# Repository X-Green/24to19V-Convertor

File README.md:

# 24to19V-Convertor

synchronous buck converter

## Chip Used

**LM3150** *From Texas Instruments* : Controller IC

**BSC070N10NS5** *From Infineon* : NMOS for switching

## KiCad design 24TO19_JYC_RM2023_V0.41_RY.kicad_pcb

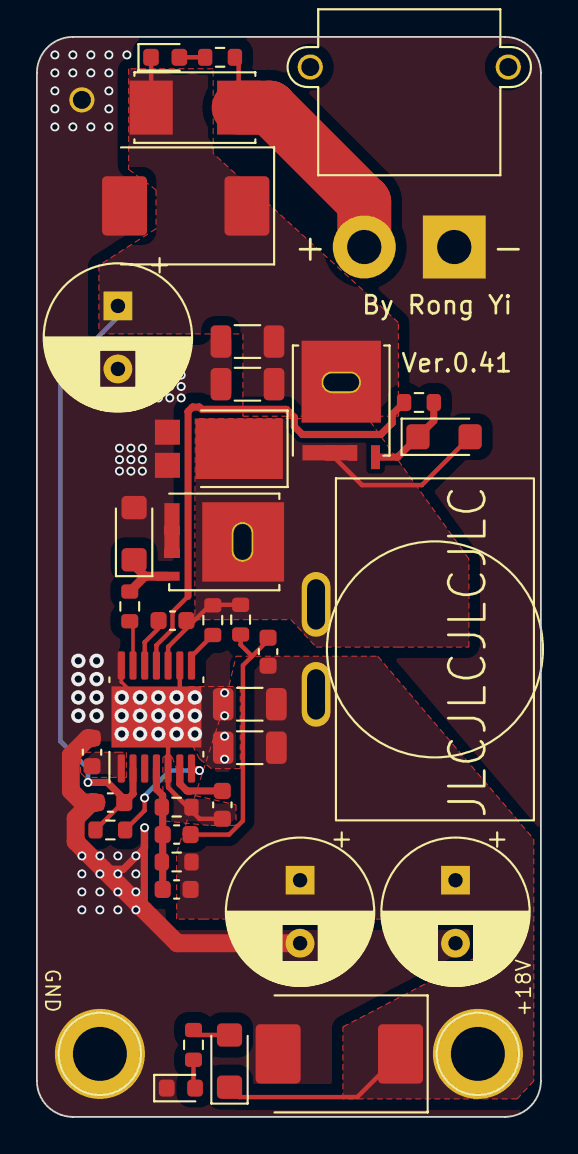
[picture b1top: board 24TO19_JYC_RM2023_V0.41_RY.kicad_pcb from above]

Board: 2 copper layers, 28.0 x 60.0 mm, 40 parts (0 on the bottom side), 19 nets.

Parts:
C1: 100nF; C_0603_1608Metric
C2: 15nF; C_0603_1608Metric
C3: 2.2uF; C_0603_1608Metric
C4, C11: 330uF; CP_Radial_D8.0mm_P3.50mm
C5: 470nF; C_0603_1608Metric
C6: 220uF; CP_Radial_D8.0mm_P3.50mm
C7: 3.9nf; C_0603_1608Metric
C8: 390pf; C_0603_1608Metric
C9, C10, C12, C13: 22uF; C_1206_3216Metric
C14: DNF; C_0603_1608Metric
D1: SMCJ18A; D_SMC
D2: SMAJ28A; D_SMC
D3, D7: LED; LED_0603_1608Metric
D4, D5, D8: SMF12A; D_SMF
D6: D_Schottky; D_PowerDI-5
F1: Fuse; Fuseholder_Littelfuse_Nano2_157x
J1: Conn_01x02; AMASS_XT30PW-M_1x02_P2.50mm_Horizontal
L1: 4.7uH; Inductor_RM6
Q1, Q2: BSC070N10NS5; TDSON-8-1
R1: 909k; R_0603_1608Metric
R2: 2.1k; R_0603_1608Metric
R3, R4: 3.3R; R_0603_1608Metric
R5: 8.06M; R_0603_1608Metric
R6: 100K; R_0603_1608Metric
R7: 287K; R_0603_1608Metric
R8: 10K; R_0603_1608Metric
R9: 1K; R_0603_1608Metric
TP1: OutputGND; TestPoint_Plated_Hole_D3.0mm
TP2: Output17V; TestPoint_Plated_Hole_D3.0mm
TP3: PowerHole; TestPoint_Plated_Hole_D2.0mm
U1: LM3150MH; HTSSOP-14-1EP_4.4x5mm_P0.65mm_EP3.4x5mm_Mask3x3.1mm

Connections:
+24V: C1.1, C6.1, C12.2, C13.2, D2.1 (A1), D7.1 (K), F1.1, Q1.5 (D), R1.2, U1.2 (VIN)
/HO: R4.1, U1.11 (HG)
/LO: R3.1, U1.13 (LG)
/SW: C5.1, D4.2 (A2), D6.1 (K), L1.1, Q1.1 (S), Q1.2 (S), Q1.3 (S), Q2.5 (D), R2.2, R5.1, U1.10 (SW)
/VOUT: C4.1, C8.2, C9.2, C10.2, C11.1, C14.2, D1.1 (A1), D8.1 (A1), L1.2, R7.2, TP2.1
BST: C5.2, U1.12 (BST)
FB: C7.1, C14.1, R7.1, R8.2, U1.4 (FB)
GND: C1.2, C2.1, C3.1, C4.2, C6.2, C9.1, C10.1, C11.2, C12.1, C13.1, D1.2 (A2), D2.2 (A2), D3.1 (K), D5.2 (A2), D6.2 (A), J1.1, Q2.1 (S), Q2.2 (S), Q2.3 (S), R8.1, TP1.1, TP3.1, U1.5 (SGND_2), U1.9 (SGND), U1.14 (PGND), U1.15 (EPAD)
ILIM: R2.1, U1.8 (ILIM)
unnamed: C7.2, C8.1, R5.2
unnamed: D3.2 (A), R9.2
unnamed: D4.1 (A1), Q1.4 (G), R4.2
unnamed: D5.1 (A1), Q2.4 (G), R3.2
unnamed: D7.2 (A), R6.2
unnamed: D8.2 (A2), R9.1
unnamed: F1.2, J1.2, R6.1
unnamed: R1.1, U1.7 (RON)
unnamed: C2.2, U1.6 (SS)
unnamed: C3.2, U1.1 (VCC)

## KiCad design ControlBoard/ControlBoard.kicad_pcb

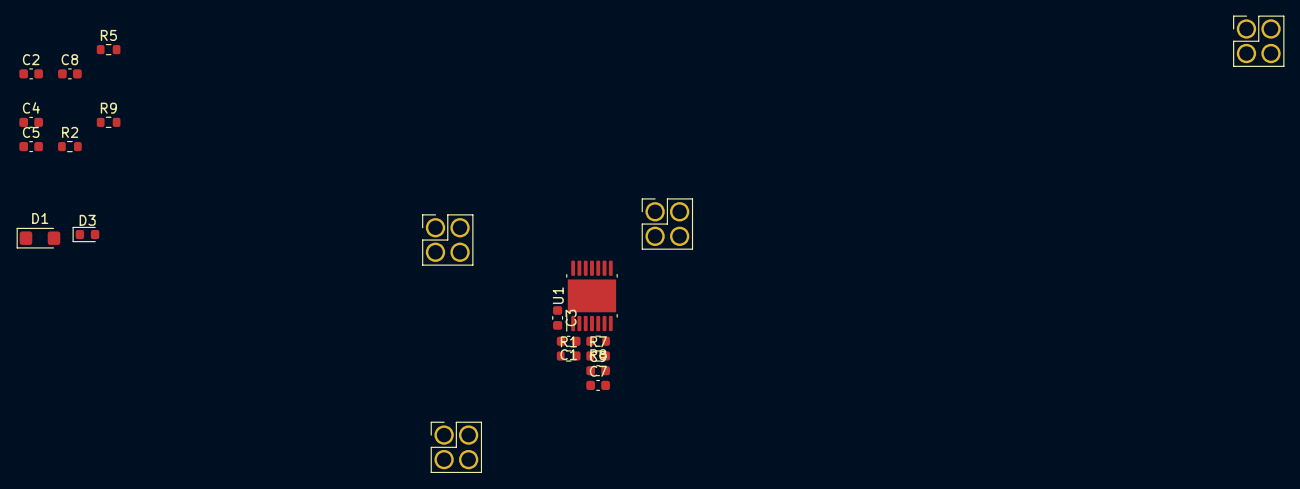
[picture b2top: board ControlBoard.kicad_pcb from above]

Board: 2 copper layers, 21 parts (0 on the bottom side), 14 nets, no tracks yet.

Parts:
C1: 100n; C_0603_1608Metric
C2: 15n; C_0603_1608Metric
C3: 2.2u; C_0603_1608Metric
C4: 22u; C_0603_1608Metric
C5: 470n; C_0603_1608Metric
C7: 3.9nf; C_0603_1608Metric
C8: 390pf; C_0603_1608Metric
C9: C_0603_1608Metric
D1: D_Schottky; D_SMF
D3: LED; LED_0603_1608Metric
J1, J2, J3, J4: Conn_02x02_Odd_Even; conn_2x02_2.54
R1: 909k; R_0603_1608Metric
R2: 2.1k; R_0603_1608Metric
R5: 8.06M; R_0603_1608Metric
R7: 309k; R_0603_1608Metric
R8: 10k; R_0603_1608Metric
R9: 300k; R_0603_1608Metric
U1: LM3150MH; HTSSOP-14-1EP_4.4x5mm_P0.65mm_EP3.4x5mm_Mask3x3.1mm

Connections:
+24V: C1.1, C4.1, J1.1, R1.2, U1.2 (VIN)
/HG: J1.4, U1.11 (HG)
/LG: J1.3, U1.13 (LG)
/SW: C5.1, J1.2, R2.2, R5.1, U1.10 (SW)
/VCC: C3.2, D1.2 (A), U1.1 (VCC)
/VOUT: C8.2, C9.2, J4.1, J4.2, J4.3, J4.4, R7.2, R9.1
BST: C5.2, D1.1 (K), U1.12 (BST)
FB: C7.1, C9.1, R7.1, R8.2, U1.4 (FB)
GND: C1.2, C2.1, C3.1, C4.2, D3.1 (K), J2.1, J2.2, J2.3, J2.4, J3.1, J3.2, J3.3, J3.4, R8.1, U1.5 (SGND_2), U1.9 (SGND), U1.14 (PGND), U1.15 (EPAD)
ILIM: R2.1, U1.8 (ILIM)
unnamed: C7.2, C8.1, R5.2
unnamed: D3.2 (A), R9.2
unnamed: R1.1, U1.7 (RON)
unnamed: C2.2, U1.6 (SS)

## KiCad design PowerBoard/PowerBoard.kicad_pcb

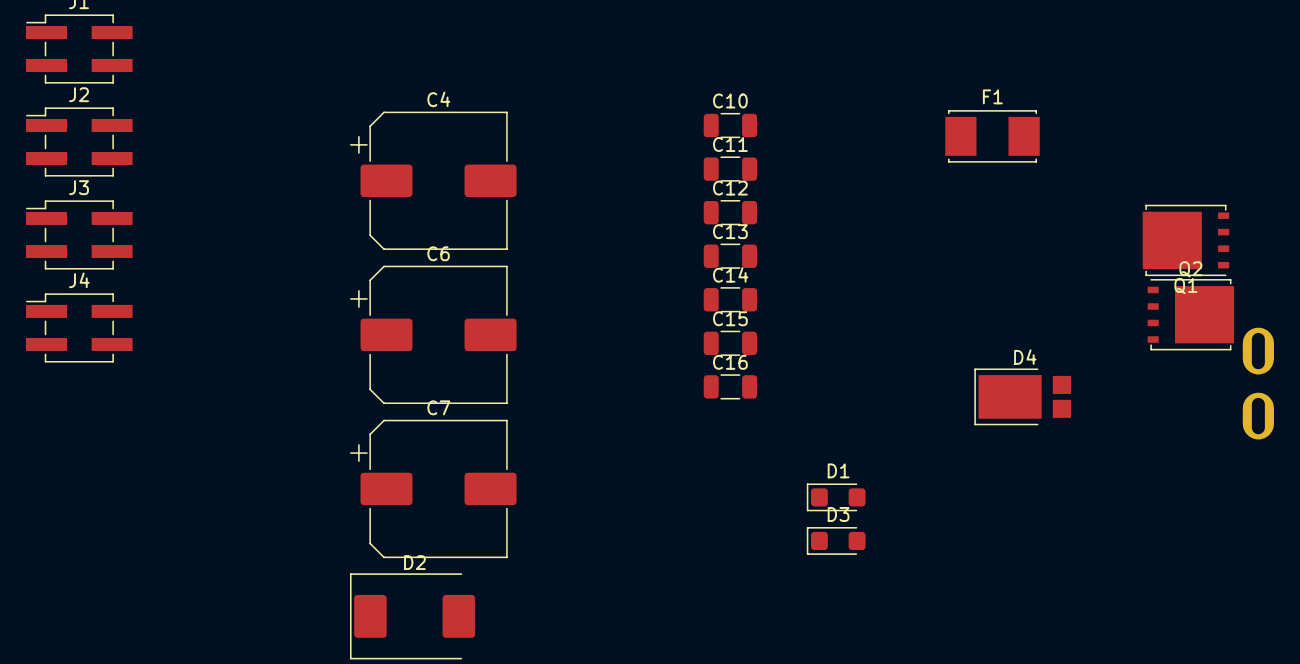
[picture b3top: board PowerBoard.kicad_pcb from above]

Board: 2 copper layers, 22 parts (0 on the bottom side), 6 nets, no tracks yet.

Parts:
C4, C6, C7: C_Polarized; CP_Elec_10x10
C10, C11, C12, C13, C14, C15, C16: 100u; C_1206_3216Metric
D1, D3: SMF12A; D_SMF
D2: SM6T30A; D_SMC
D4: D_Schottky; D_PowerDI-5
F1: Fuse; Fuseholder_Littelfuse_Nano2_157x
J1, J2, J3, J4: Conn_02x02_Odd_Even; PinHeader_2x02_P2.54mm_Vertical_SMD
L1: 10uh; Inductor_RM6
Q1, Q2: BSC070N10NS5; TDSON-8-1

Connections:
+24V: C6.1, C14.2, C15.2, C16.2, D2.1 (A1), F1.2, J1.1, Q1.5 (D)
/HG: D1.1 (A1), J1.4, Q1.4 (G)
/LG: D3.1 (A1), J1.3, Q2.4 (G)
/SW: D1.2 (A2), D4.1 (K), J1.2, L1.1, Q1.1 (S), Q1.2 (S), Q1.3 (S), Q2.5 (D)
/VOUT: C4.1, C7.1, C10.2, C11.2, C12.2, C13.2, J3.1, J3.2, J3.3, J3.4, L1.2
GND: C4.2, C6.2, C7.2, C10.1, C11.1, C12.1, C13.1, C14.1, C15.1, C16.1, D2.2 (A2), D3.2 (A2), D4.2 (A), J2.1, J2.2, J2.3, J2.4, J4.1, J4.2, J4.3, J4.4, Q2.1 (S), Q2.2 (S), Q2.3 (S)

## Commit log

2023-02-07 init
2023-02-07 Create README.md
    Add readme
2023-02-07 new ver
2023-02-09 Sch v1.0
2023-02-09 rm2023 hardware core lib download
2023-02-09 configure rm2023 libs
2023-02-19 Use JYC Design
2023-06-21 ver0.4 layout done
2023-06-25 decoration location adjustment build
2023-07-07 Updating to ver 0.41: Changed Caps to THT; Decreased total area. Layout done. Routing pending.
2023-07-08 v0.41 done
